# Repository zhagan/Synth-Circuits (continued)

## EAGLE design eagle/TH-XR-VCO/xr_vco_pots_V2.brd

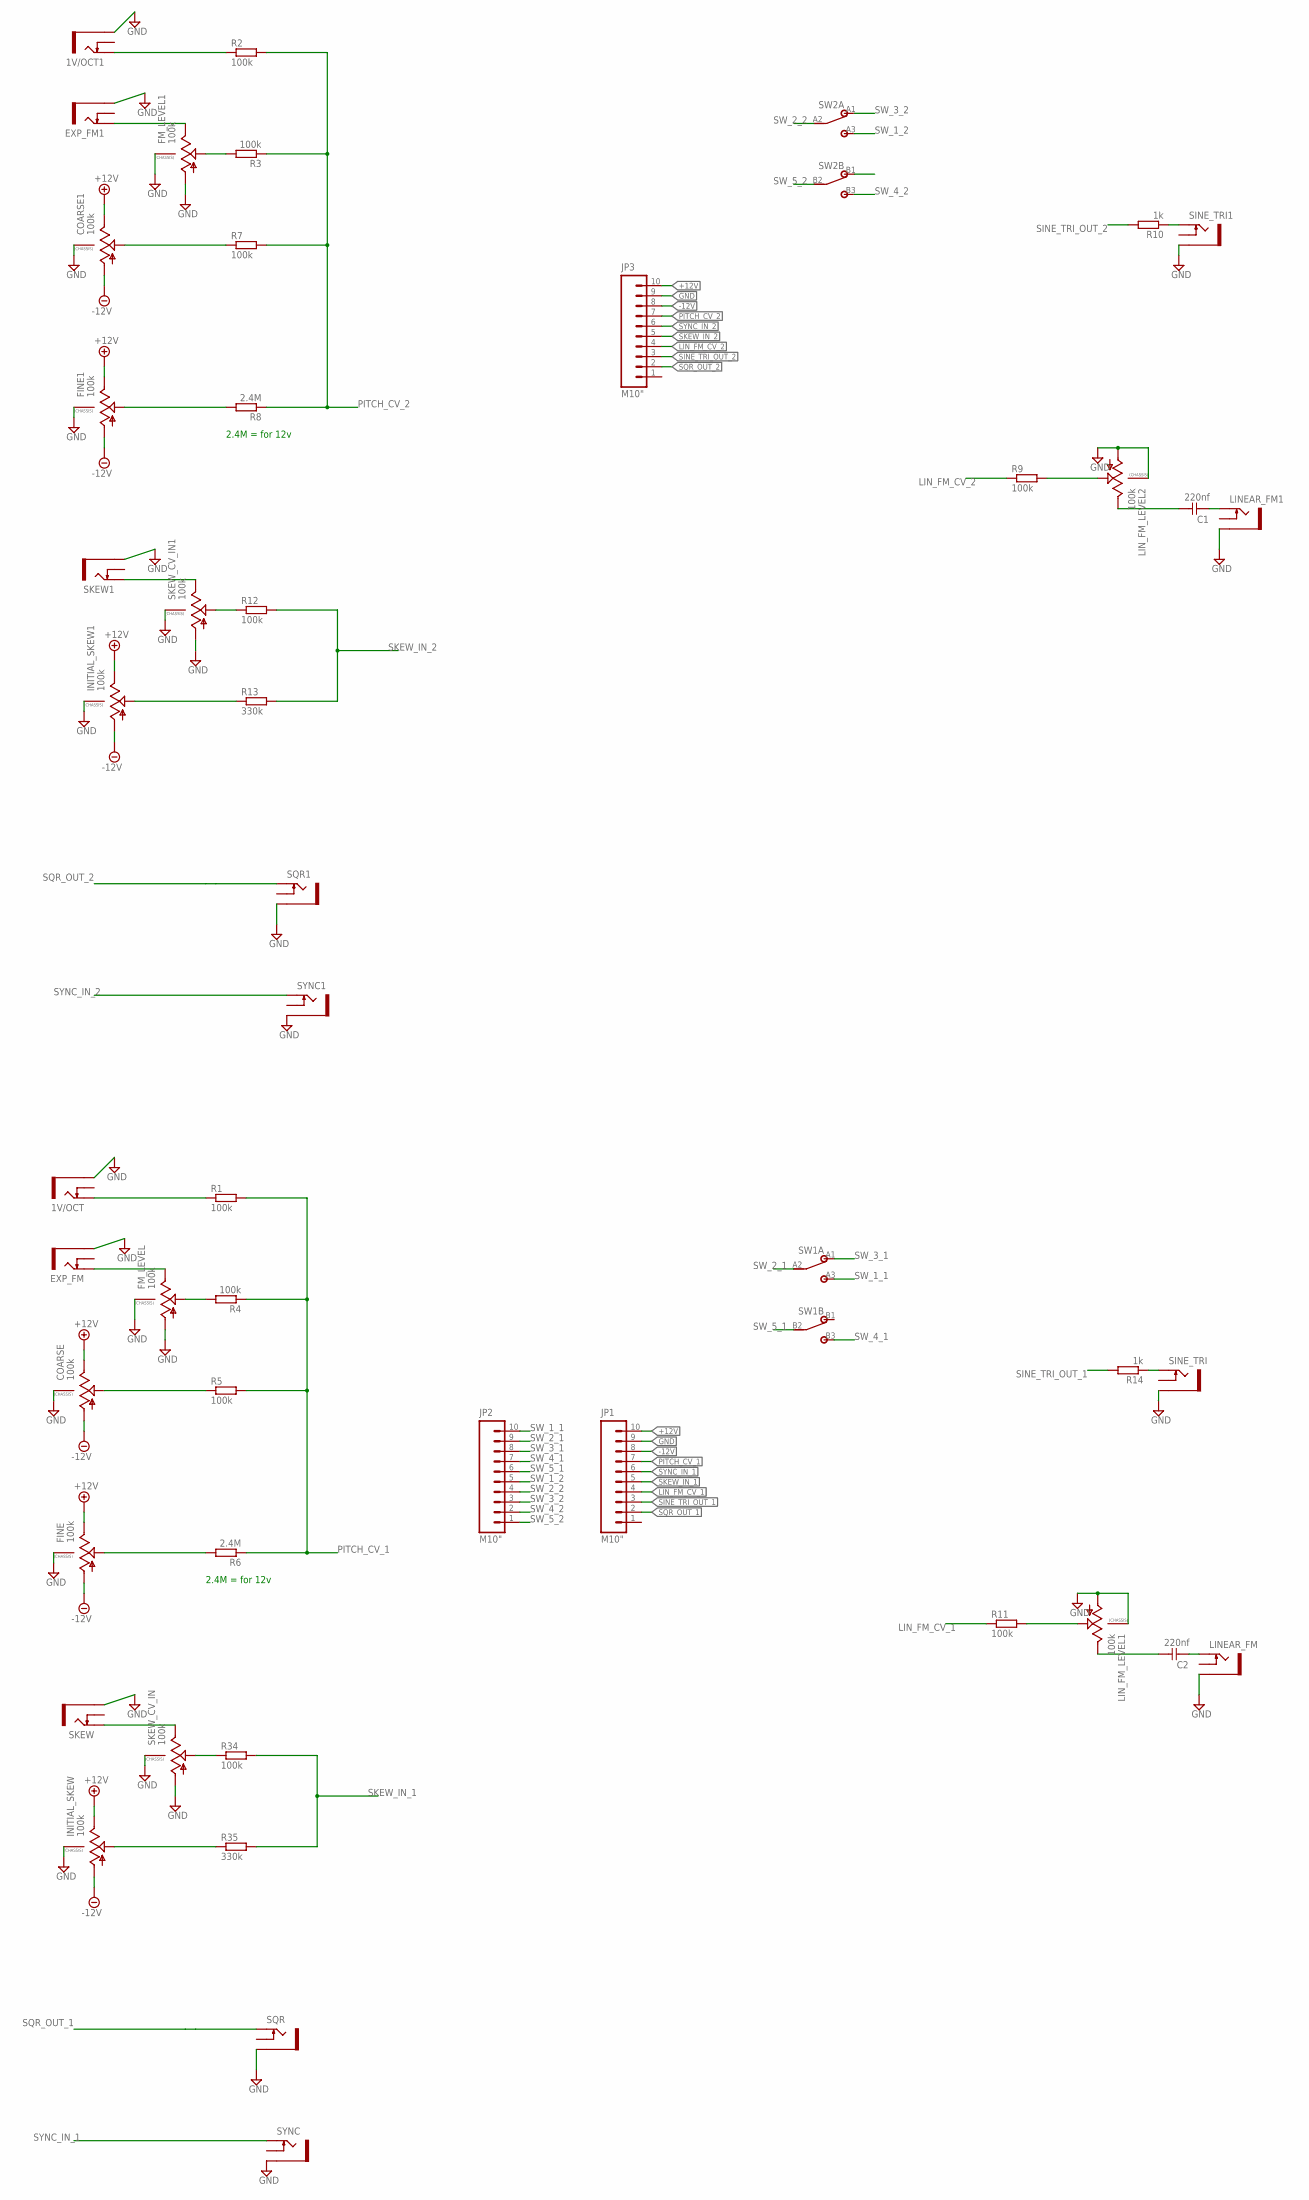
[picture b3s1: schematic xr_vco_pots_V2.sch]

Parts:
1V/OCT, 1V/OCT1: THONKICONNNEW; WQP-PJ301M-12_JACK
C1, C2: 220nf; C050-024X044
COARSE, COARSE1: 100k; 9MM_SNAP-IN_POT
EXP_FM, EXP_FM1: THONKICONNNEW; WQP-PJ301M-12_JACK
FINE, FINE1: 100k; 9MM_SNAP-IN_POT
FM_LEVEL, FM_LEVEL1: 100k; 9MM_SNAP-IN_POT
INITIAL_SKEW, INITIAL_SKEW1: 100k; 9MM_SNAP-IN_POT
JP1, JP2, JP3: M10"; 1X10
LINEAR_FM, LINEAR_FM1: THONKICONNNEW; WQP-PJ301M-12_JACK
LIN_FM_LEVEL1, LIN_FM_LEVEL2: 100k; 9MM_SNAP-IN_POT
R1, R2, R3, R4, R5, R7, R9, R11, R12, R34: 100k; 7MM_RESISTOR
R6, R8: 2.4M; 7MM_RESISTOR
R10, R14: 1k; 7MM_RESISTOR
R13, R35: 330k; 7MM_RESISTOR
SINE_TRI, SINE_TRI1: THONKICONNNEW; WQP-PJ301M-12_JACK
SKEW, SKEW1: THONKICONNNEW; WQP-PJ301M-12_JACK
SKEW_CV_IN, SKEW_CV_IN1: 100k; 9MM_SNAP-IN_POT
SQR, SQR1: THONKICONNNEW; WQP-PJ301M-12_JACK
SW1, SW2: DPDT
SYNC, SYNC1: THONKICONNNEW; WQP-PJ301M-12_JACK

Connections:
+12V: COARSE.3 (E), COARSE1.3 (E), FINE.3 (E), FINE1.3 (E), INITIAL_SKEW.3 (E), INITIAL_SKEW1.3 (E), JP1.10, JP3.10
-12V: COARSE.1 (A), COARSE1.1 (A), FINE.1 (A), FINE1.1 (A), INITIAL_SKEW.1 (A), INITIAL_SKEW1.1 (A), JP1.8, JP3.8
GND: 1V/OCT.P$3_SLEEVE (SLEEVE), 1V/OCT1.P$3_SLEEVE (SLEEVE), COARSE.CHASSIS2, COARSE1.CHASSIS2, EXP_FM.P$3_SLEEVE (SLEEVE), EXP_FM1.P$3_SLEEVE (SLEEVE), FINE.CHASSIS2, FINE1.CHASSIS2, FM_LEVEL.1 (A), FM_LEVEL.CHASSIS2, FM_LEVEL1.1 (A), FM_LEVEL1.CHASSIS2, INITIAL_SKEW.CHASSIS2, INITIAL_SKEW1.CHASSIS2, JP1.9, JP3.9, LINEAR_FM.P$3_SLEEVE (SLEEVE), LINEAR_FM1.P$3_SLEEVE (SLEEVE), LIN_FM_LEVEL1.1 (A), LIN_FM_LEVEL1.CHASSIS2, LIN_FM_LEVEL2.1 (A), LIN_FM_LEVEL2.CHASSIS2, SINE_TRI.P$3_SLEEVE (SLEEVE), SINE_TRI1.P$3_SLEEVE (SLEEVE), SKEW.P$3_SLEEVE (SLEEVE), SKEW1.P$3_SLEEVE (SLEEVE), SKEW_CV_IN.1 (A), SKEW_CV_IN.CHASSIS2, SKEW_CV_IN1.1 (A), SKEW_CV_IN1.CHASSIS2, SQR.P$3_SLEEVE (SLEEVE), SQR1.P$3_SLEEVE (SLEEVE), SYNC.P$3_SLEEVE (SLEEVE), SYNC1.P$3_SLEEVE (SLEEVE)
LIN_FM_CV_1: JP1.4, R11.1
LIN_FM_CV_2: JP3.4, R9.1
unnamed: 1V/OCT.P$1_TIP (TIP), R1.1
unnamed: EXP_FM.P$1_TIP (TIP), FM_LEVEL.3 (E)
unnamed: FM_LEVEL.2 (S), R4.2
unnamed: COARSE.2 (S), R5.1
unnamed: FINE.2 (S), R6.2
unnamed: 1V/OCT1.P$1_TIP (TIP), R2.1
unnamed: EXP_FM1.P$1_TIP (TIP), FM_LEVEL1.3 (E)
unnamed: FM_LEVEL1.2 (S), R3.2
unnamed: COARSE1.2 (S), R7.1
unnamed: FINE1.2 (S), R8.2
unnamed: LIN_FM_LEVEL2.2 (S), R9.2
unnamed: C1.1, LIN_FM_LEVEL2.3 (E)
unnamed: C1.2, LINEAR_FM1.P$1_TIP (TIP)
unnamed: R10.1, SINE_TRI1.P$1_TIP (TIP)
unnamed: SKEW1.P$1_TIP (TIP), SKEW_CV_IN1.3 (E)
unnamed: R12.1, SKEW_CV_IN1.2 (S)
unnamed: LIN_FM_LEVEL1.2 (S), R11.2
unnamed: R14.1, SINE_TRI.P$1_TIP (TIP)
unnamed: C2.1, LIN_FM_LEVEL1.3 (E)
unnamed: C2.2, LINEAR_FM.P$1_TIP (TIP)
unnamed: INITIAL_SKEW1.2 (S), R13.1
unnamed: SKEW.P$1_TIP (TIP), SKEW_CV_IN.3 (E)
unnamed: R34.1, SKEW_CV_IN.2 (S)
unnamed: INITIAL_SKEW.2 (S), R35.1
PITCH_CV_1: JP1.7, R1.2, R4.1, R5.2, R6.1
PITCH_CV_2: JP3.7, R2.2, R3.1, R7.2, R8.1
SINE_TRI_OUT_1: JP1.3, R14.2
SINE_TRI_OUT_2: JP3.3, R10.2
SKEW_IN_1: JP1.5, R34.2, R35.2
SKEW_IN_2: JP3.5, R12.2, R13.2
SQR_OUT_1: JP1.2, SQR.P$1_TIP (TIP)
SQR_OUT_2: JP3.2, SQR1.P$1_TIP (TIP)
SW_1_1: JP2.10, SW1.A3 (3)
SW_1_2: JP2.5, SW2.A3 (3)
SW_2_1: JP2.9, SW1.A2 (2)
SW_2_2: JP2.4, SW2.A2 (2)
SW_3_1: JP2.8, SW1.A1 (1)
SW_3_2: JP2.3, SW2.A1 (1)
SW_4_1: JP2.7, SW1.B3 (3)
SW_4_2: JP2.2, SW2.B3 (3)
SW_5_1: JP2.6, SW1.B2 (2)
SW_5_2: JP2.1, SW2.B2 (2)
SW_6: SW2.B1 (1)
SYNC_IN_1: JP1.6, SYNC.P$1_TIP (TIP)
SYNC_IN_2: JP3.6, SYNC1.P$1_TIP (TIP)

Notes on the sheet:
2.4M = for 12v

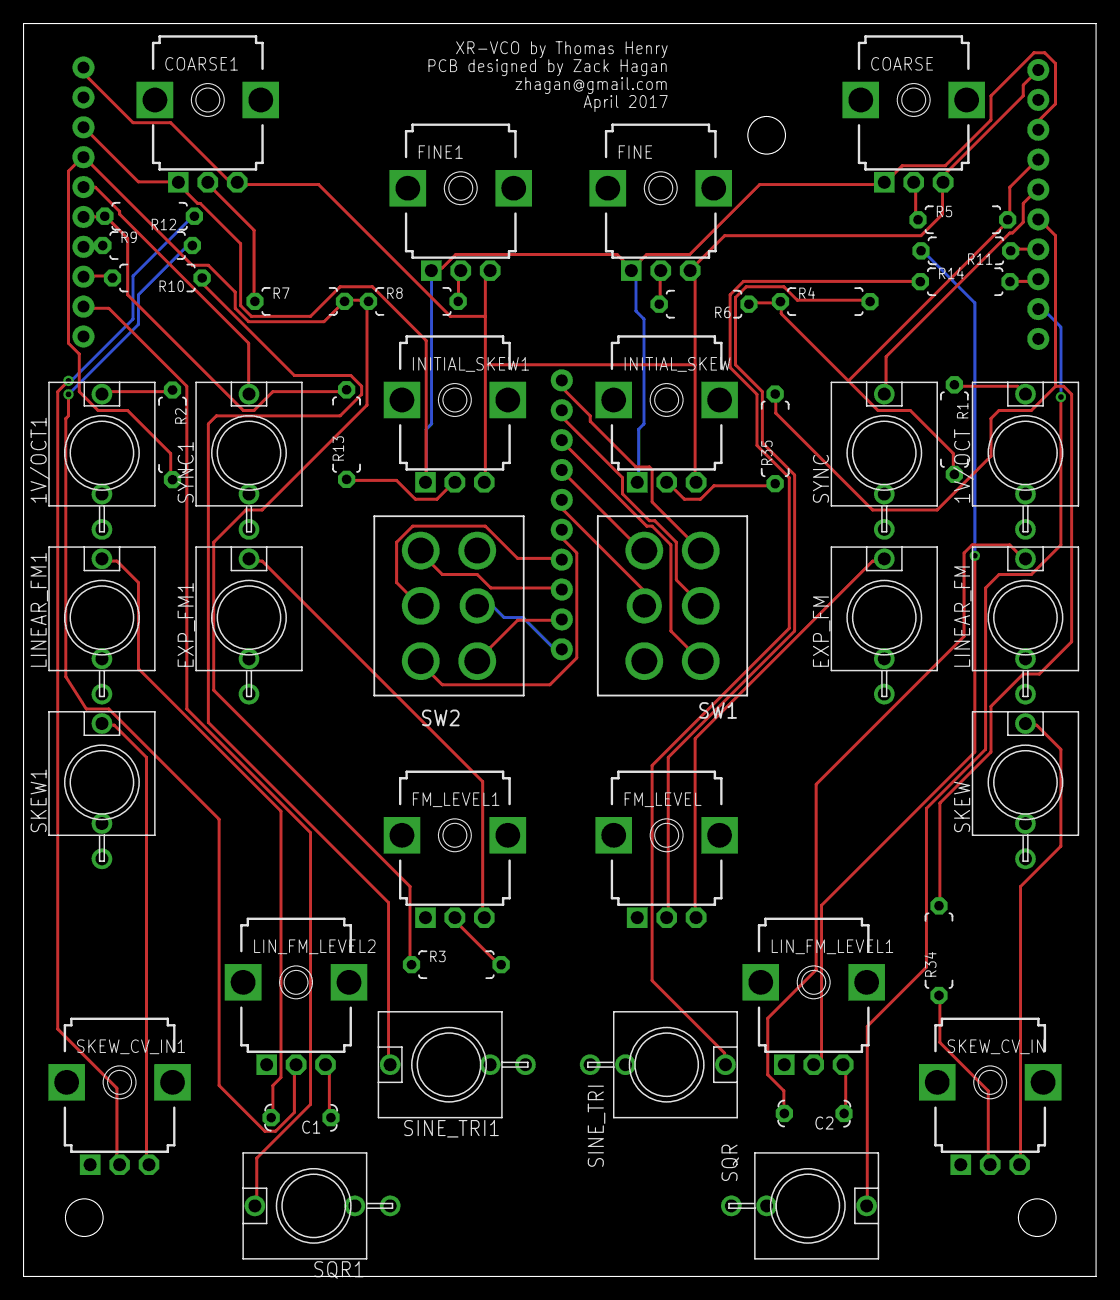
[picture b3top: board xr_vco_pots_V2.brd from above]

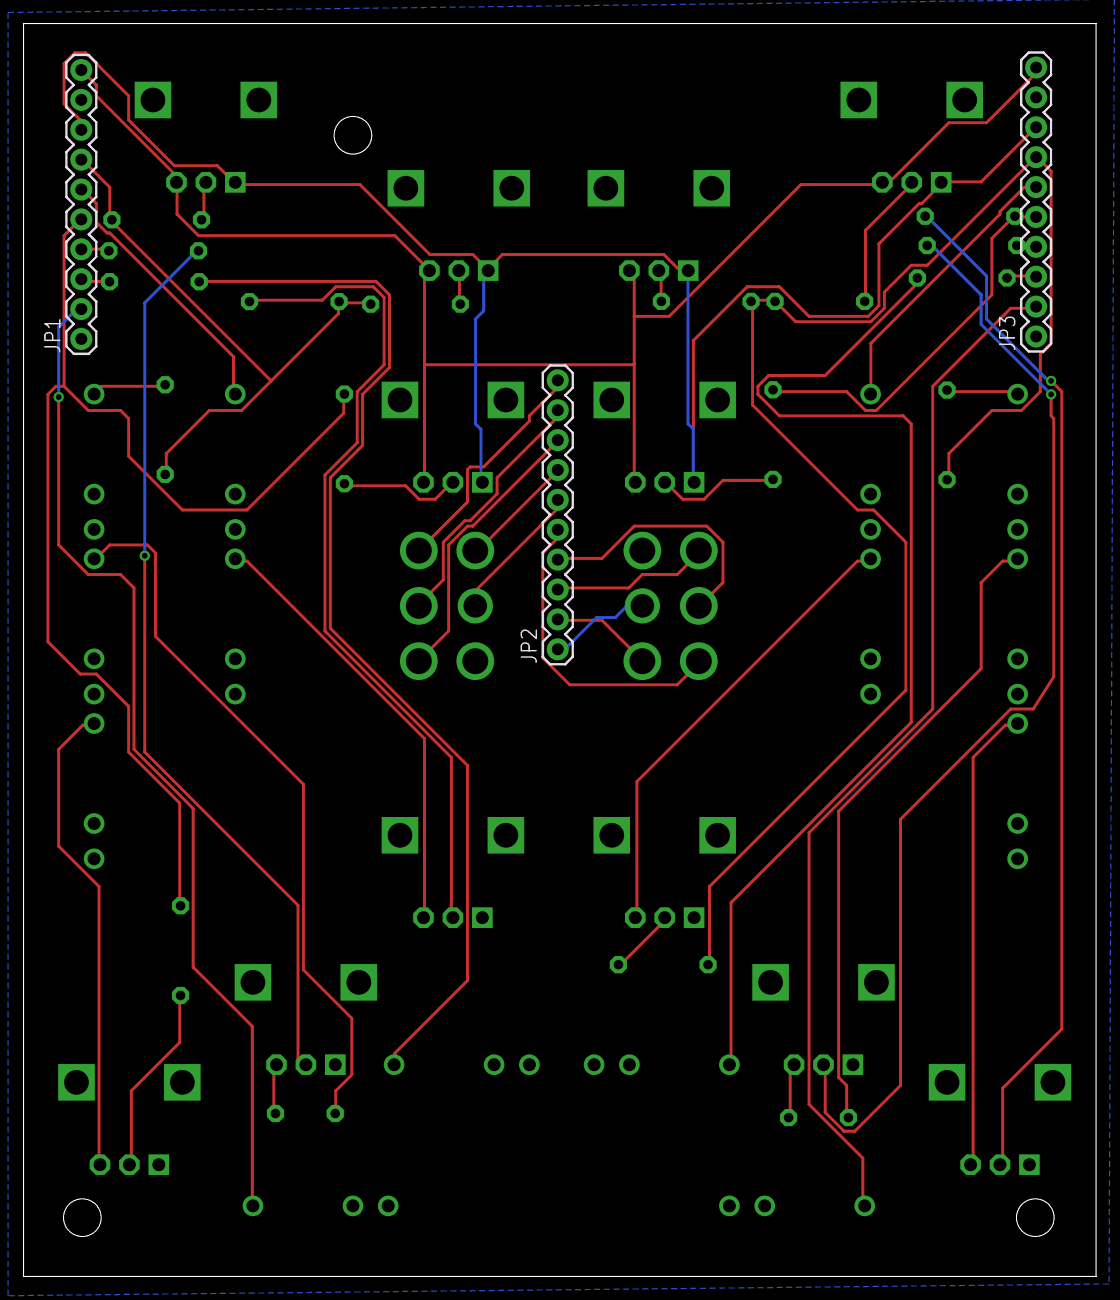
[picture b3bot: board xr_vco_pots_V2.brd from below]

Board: 2 copper layers, 91.2 x 106.5 mm, 52 parts (3 on the bottom side), 49 nets.

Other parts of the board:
U$1, U$3, U$4: MOUNTING_HOLE

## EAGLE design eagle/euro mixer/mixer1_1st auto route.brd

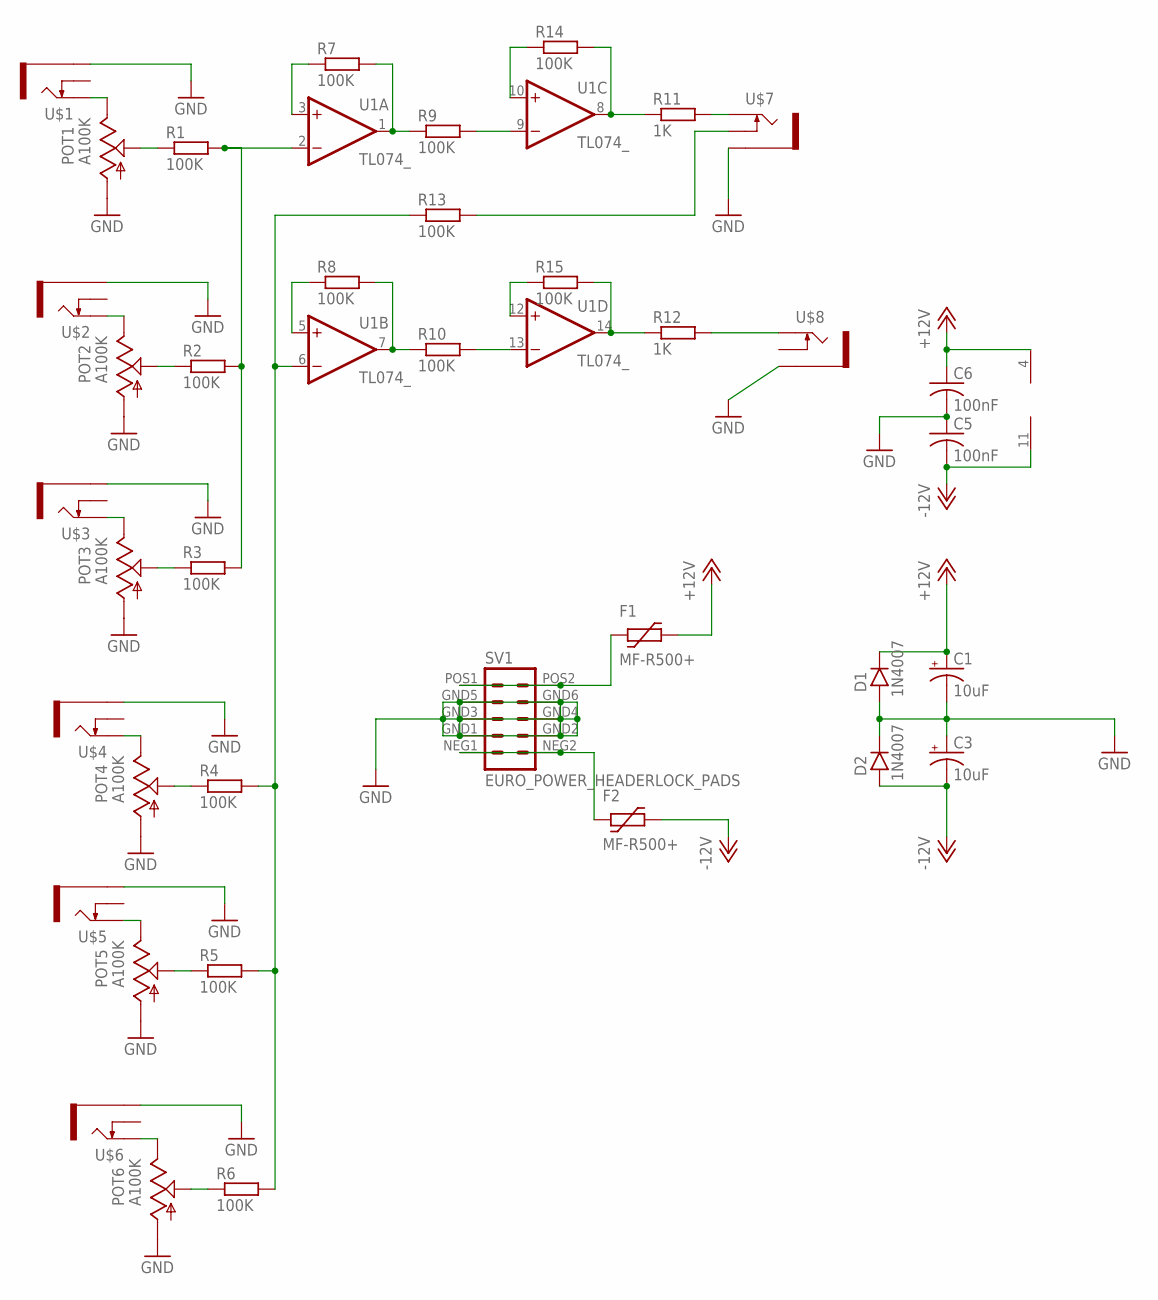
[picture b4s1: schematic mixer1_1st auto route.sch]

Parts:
C1, C3: 10uF; E2,5-7
C5, C6: 100nF; C075-032X103
D1, D2: 1N4007; DO41-3
F1, F2: MF-R500+; BOURNS-MF-R
POT1, POT2, POT3, POT4, POT5, POT6: A100K; 9MM_SNAP-IN_POT
R1, R2, R3, R4, R5, R6, R7, R8, R9, R10, R13, R14, R15: 100K; 7MM_RESISTOR
R11, R12: 1K; 7MM_RESISTOR
SV1: EURO_POWER_HEADERLOCK_PADS; EURO_PWR_HEADER_LOCK
U1: TL074_; DIL14
U$1, U$2, U$3, U$4, U$5, U$6, U$7, U$8: THONKICONNNEW; WQP-PJ301M-12_JACK

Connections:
+12V: C1.+, C6.1, D1.C, F1.P$2 (2), U1.4 (V+)
-12V: C3.-, C5.2, D2.A, F2.P$2 (2), U1.11 (V-)
GND: C1.-, C3.+, C5.1, C6.2, D1.A, D2.C, POT1.1 (A), POT2.1 (A), POT3.1 (A), POT4.1 (A), POT5.1 (A), POT6.1 (A), SV1.GND1 (4), SV1.GND2 (3), SV1.GND3 (6), SV1.GND4 (5), SV1.GND5 (8), SV1.GND6 (7), U$1.P$3_SLEEVE (SLEEVE), U$2.P$3_SLEEVE (SLEEVE), U$3.P$3_SLEEVE (SLEEVE), U$4.P$3_SLEEVE (SLEEVE), U$5.P$3_SLEEVE (SLEEVE), U$6.P$3_SLEEVE (SLEEVE), U$7.P$3_SLEEVE (SLEEVE), U$8.P$3_SLEEVE (SLEEVE)
unnamed: POT2.3 (E), U$2.P$1_TIP (TIP)
unnamed: POT2.2 (S), R2.1
unnamed: POT1.3 (E), U$1.P$1_TIP (TIP)
unnamed: POT1.2 (S), R1.1
unnamed: POT3.3 (E), U$3.P$1_TIP (TIP)
unnamed: POT3.2 (S), R3.1
unnamed: POT4.3 (E), U$4.P$1_TIP (TIP)
unnamed: POT4.2 (S), R4.1
unnamed: POT5.3 (E), U$5.P$1_TIP (TIP)
unnamed: POT5.2 (S), R5.1
unnamed: POT6.3 (E), U$6.P$1_TIP (TIP)
unnamed: POT6.2 (S), R6.1
unnamed: R1.2, R2.2, R3.2, U1.2 (-IN)
unnamed: R7.1, U1.3 (+IN)
unnamed: R7.2, R9.1, U1.1 (OUT)
unnamed: R9.2, U1.9 (-IN)
unnamed: R14.1, U1.10 (+IN)
unnamed: R11.2, U$7.P$1_TIP (TIP)
unnamed: R8.2, R10.1, U1.7 (OUT)
unnamed: R8.1, U1.5 (+IN)
unnamed: R15.1, U1.12 (+IN)
unnamed: R12.1, R15.2, U1.14 (OUT)
unnamed: R10.2, U1.13 (-IN)
unnamed: R4.2, R5.2, R6.2, R13.1, U1.6 (-IN)
unnamed: R11.1, R14.2, U1.8 (OUT)
unnamed: R13.2, U$7.P$2_SWITCH (SWITCH)
unnamed: R12.2, U$8.P$1_TIP (TIP)
unnamed: F2.P$1 (1), SV1.NEG1 (2), SV1.NEG2 (1)
unnamed: F1.P$1 (1), SV1.POS1 (10), SV1.POS2 (9)

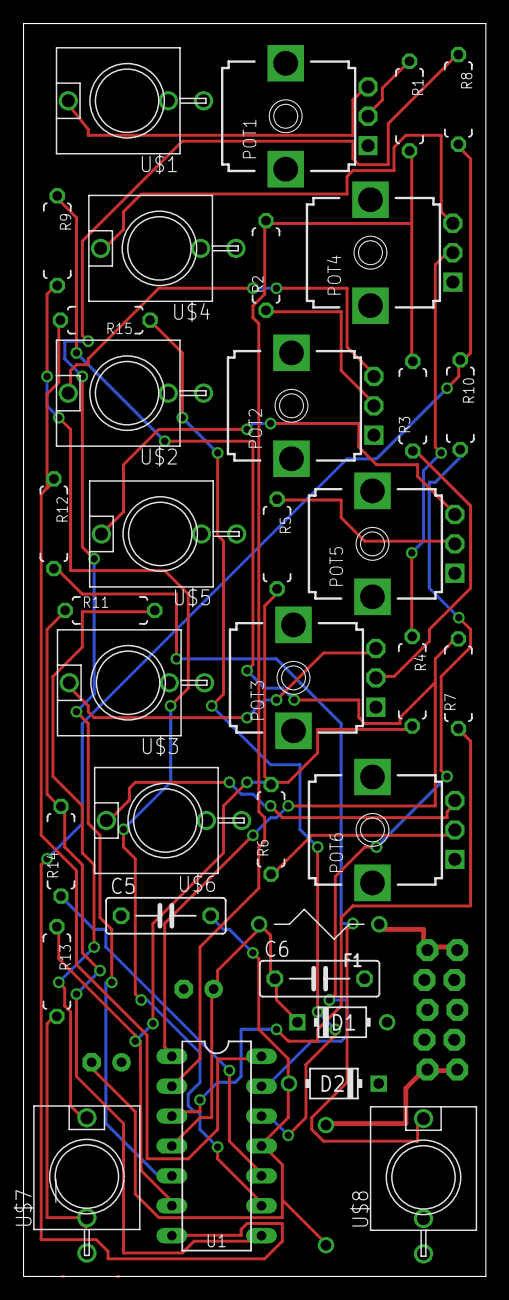
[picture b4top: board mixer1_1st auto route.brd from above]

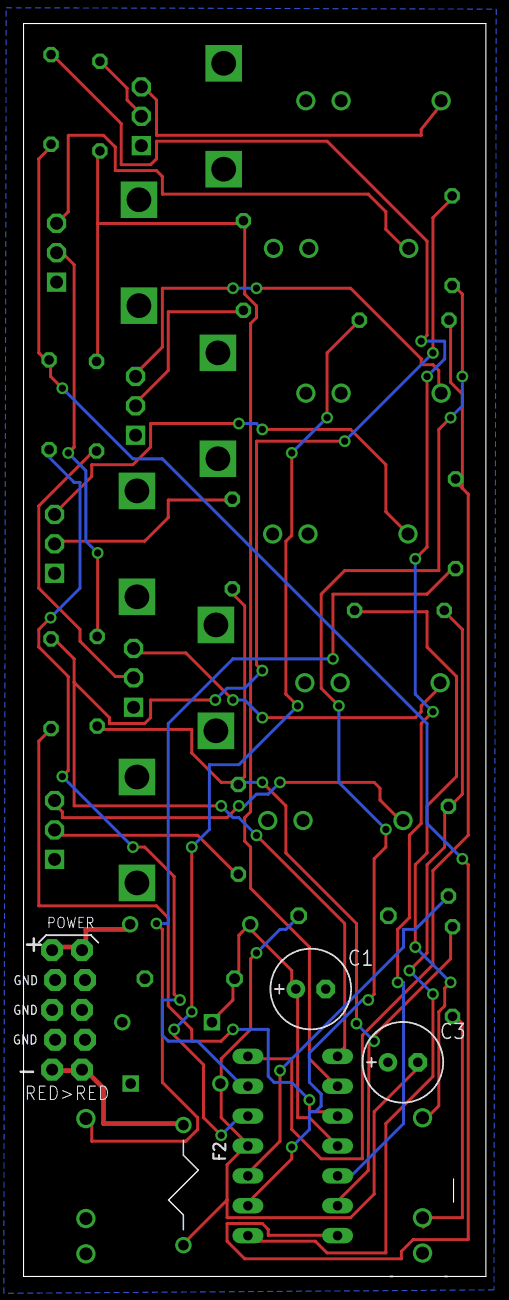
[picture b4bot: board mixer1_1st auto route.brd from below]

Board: 2 copper layers, 39.3 x 106.5 mm, 39 parts (4 on the bottom side), 32 nets.

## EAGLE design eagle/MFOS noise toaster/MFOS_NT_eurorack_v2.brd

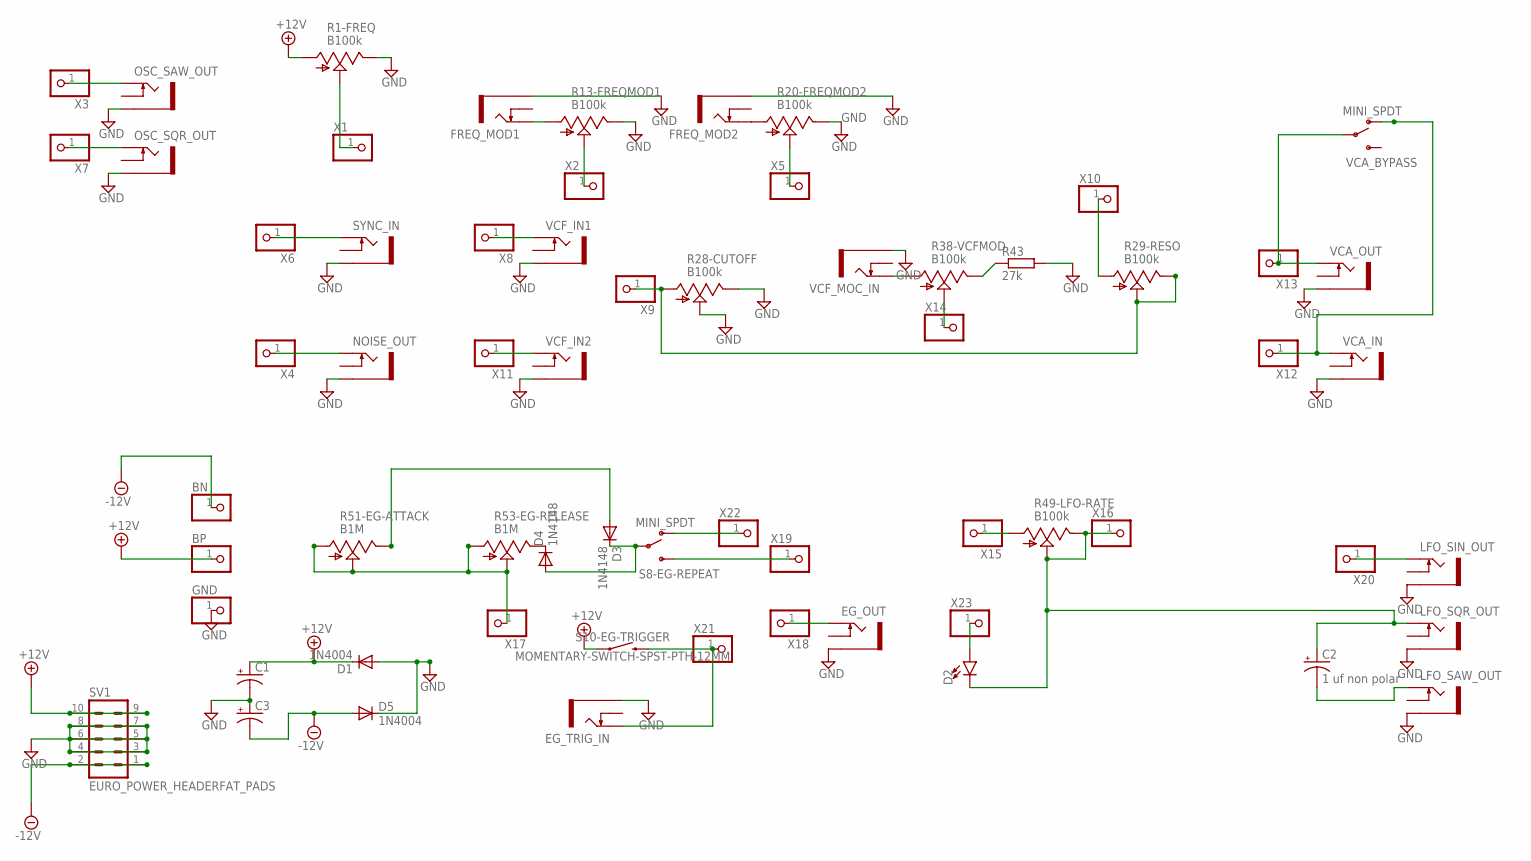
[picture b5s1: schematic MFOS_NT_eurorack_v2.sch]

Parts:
BN: PINHD-1X1; 1X01
BP: PINHD-1X1; 1X01
C1, C3: CPOL-USE2.5-7; E2,5-7
C2: 1 uf non polar; TT2D5L
D1, D5: 1N4004; DO41-10
D2: LED3MM; LED_3MM
D3, D4: 1N4148; DO35-7
EG_OUT: THONKICONNNEW; WQP-PJ301M-12_JACK
EG_TRIG_IN: THONKICONNNEW; WQP-PJ301M-12_JACK
FREQ_MOD1, FREQ_MOD2: THONKICONNNEW; WQP-PJ301M-12_JACK
GND: PINHD-1X1; 1X01
LFO_SAW_OUT: THONKICONNNEW; WQP-PJ301M-12_JACK
LFO_SIN_OUT: THONKICONNNEW; WQP-PJ301M-12_JACK
LFO_SQR_OUT: THONKICONNNEW; WQP-PJ301M-12_JACK
NOISE_OUT: THONKICONNNEW; WQP-PJ301M-12_JACK
OSC_SAW_OUT: THONKICONNNEW; WQP-PJ301M-12_JACK
OSC_SQR_OUT: THONKICONNNEW; WQP-PJ301M-12_JACK
R1-FREQ, R13-FREQMOD1, R20-FREQMOD2, R28-CUTOFF, R29-RESO, R38-VCFMOD, R49-LFO-RATE: B100k; 9MM_SNAP-IN_POT
R43: 27k; 7MM_RESISTOR
R51-EG-ATTACK, R53-EG-RELEASE: B1M; 9MM_SNAP-IN_POT
S8-EG-REPEAT: MINI_SPDT; MINI_SPDT_RIGHTANGLE
S10-EG-TRIGGER: MOMENTARY-SWITCH-SPST-PTH-12MM; TACTILE_SWITCH_PTH_12MM
SV1: EURO_POWER_HEADERFAT_PADS; EURO_PWR_HEADER_FAT
SYNC_IN: THONKICONNNEW; WQP-PJ301M-12_JACK
VCA_BYPASS: MINI_SPDT; MINI_SPDT_RIGHTANGLE
VCA_IN: THONKICONNNEW; WQP-PJ301M-12_JACK
VCA_OUT: THONKICONNNEW; WQP-PJ301M-12_JACK
VCF_IN1, VCF_IN2: THONKICONNNEW; WQP-PJ301M-12_JACK
VCF_MOC_IN: THONKICONNNEW; WQP-PJ301M-12_JACK
X1, X2, X3, X4, X5, X6, X7, X8, X9, X10, X11, X12, X13, X14, X15, X16, X17, X18, X19, X20, X21, X22, X23: PINHD-1X1; 1X01

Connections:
+12V: BP.1, C1.+, D1.C, R1-FREQ.1 (A), S10-EG-TRIGGER.1, SV1.9, SV1.10
-12V: BN.1, C3.-, D5.A, SV1.1, SV1.2
GND: C1.-, C3.+, D1.A, D5.C, EG_OUT.P$3_SLEEVE (SLEEVE), EG_TRIG_IN.P$3_SLEEVE (SLEEVE), FREQ_MOD1.P$3_SLEEVE (SLEEVE), FREQ_MOD2.P$3_SLEEVE (SLEEVE), GND.1, LFO_SAW_OUT.P$3_SLEEVE (SLEEVE), LFO_SIN_OUT.P$3_SLEEVE (SLEEVE), LFO_SQR_OUT.P$3_SLEEVE (SLEEVE), NOISE_OUT.P$3_SLEEVE (SLEEVE), OSC_SAW_OUT.P$3_SLEEVE (SLEEVE), OSC_SQR_OUT.P$3_SLEEVE (SLEEVE), R1-FREQ.3 (E), R13-FREQMOD1.3 (E), R20-FREQMOD2.3 (E), R28-CUTOFF.2 (S), R28-CUTOFF.3 (E), R43.2, SV1.3, SV1.4, SV1.5, SV1.6, SV1.7, SV1.8, SYNC_IN.P$3_SLEEVE (SLEEVE), VCA_IN.P$3_SLEEVE (SLEEVE), VCA_OUT.P$3_SLEEVE (SLEEVE), VCF_IN1.P$3_SLEEVE (SLEEVE), VCF_IN2.P$3_SLEEVE (SLEEVE), VCF_MOC_IN.P$3_SLEEVE (SLEEVE)
unnamed: R1-FREQ.2 (S), X1.1
unnamed: FREQ_MOD1.P$1_TIP (TIP), R13-FREQMOD1.1 (A)
unnamed: FREQ_MOD2.P$1_TIP (TIP), R20-FREQMOD2.1 (A)
unnamed: R13-FREQMOD1.2 (S), X2.1
unnamed: R20-FREQMOD2.2 (S), X5.1
unnamed: SYNC_IN.P$1_TIP (TIP), X6.1
unnamed: OSC_SAW_OUT.P$1_TIP (TIP), X3.1
unnamed: OSC_SQR_OUT.P$1_TIP (TIP), X7.1
unnamed: NOISE_OUT.P$1_TIP (TIP), X4.1
unnamed: VCF_IN1.P$1_TIP (TIP), X8.1
unnamed: VCF_IN2.P$1_TIP (TIP), X11.1
unnamed: R28-CUTOFF.1 (A), R29-RESO.2 (S), R29-RESO.3 (E), X9.1
unnamed: R38-VCFMOD.3 (E), R43.1
unnamed: R29-RESO.1 (A), X10.1
unnamed: R38-VCFMOD.2 (S), X14.1
unnamed: R38-VCFMOD.1 (A), VCF_MOC_IN.P$1_TIP (TIP)
unnamed: VCA_BYPASS.UP (O), VCA_IN.P$1_TIP (TIP), X12.1
unnamed: VCA_BYPASS.COMMON, VCA_OUT.P$1_TIP (TIP), X13.1
unnamed: EG_TRIG_IN.P$1_TIP (TIP), S10-EG-TRIGGER.3 (2), X21.1
unnamed: R51-EG-ATTACK.1 (A), R51-EG-ATTACK.2 (S), R53-EG-RELEASE.1 (A), R53-EG-RELEASE.2 (S), X17.1
unnamed: D4.C, R53-EG-RELEASE.3 (E)
unnamed: D3.C, D4.A, S8-EG-REPEAT.COMMON
unnamed: S8-EG-REPEAT.DOWN (S), X19.1
unnamed: D3.A, R51-EG-ATTACK.3 (E)
unnamed: S8-EG-REPEAT.UP (O), X22.1
unnamed: EG_OUT.P$1_TIP (TIP), X18.1
unnamed: R49-LFO-RATE.1 (A), X15.1
unnamed: C2.+, D2.K (C), LFO_SQR_OUT.P$1_TIP (TIP), R49-LFO-RATE.2 (S), R49-LFO-RATE.3 (E), X16.1
unnamed: C2.-, LFO_SAW_OUT.P$1_TIP (TIP)
unnamed: LFO_SIN_OUT.P$1_TIP (TIP), X20.1
unnamed: D2.A, X23.1

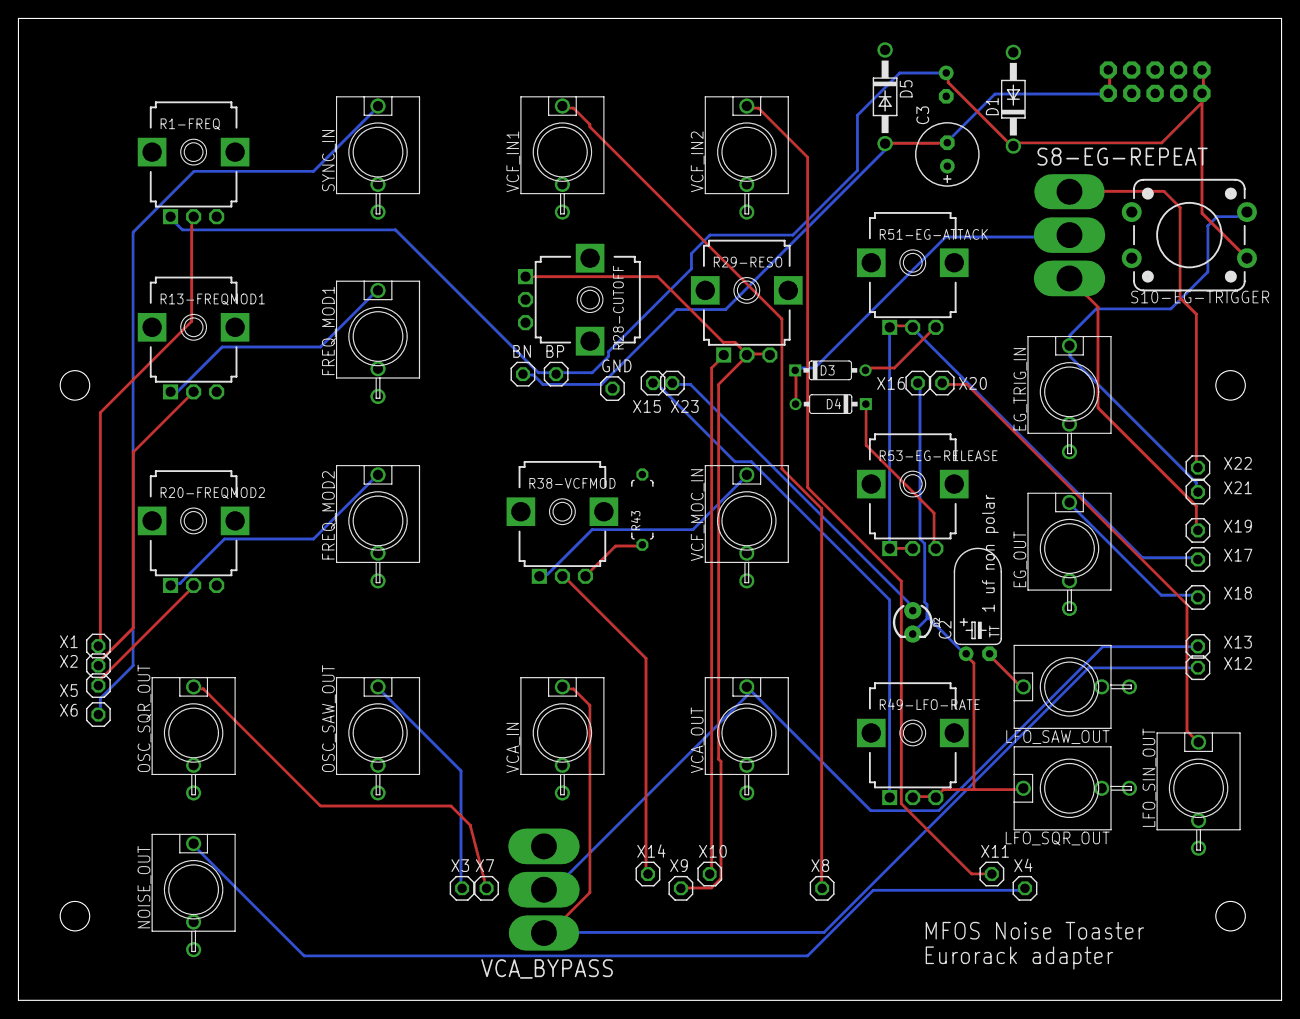
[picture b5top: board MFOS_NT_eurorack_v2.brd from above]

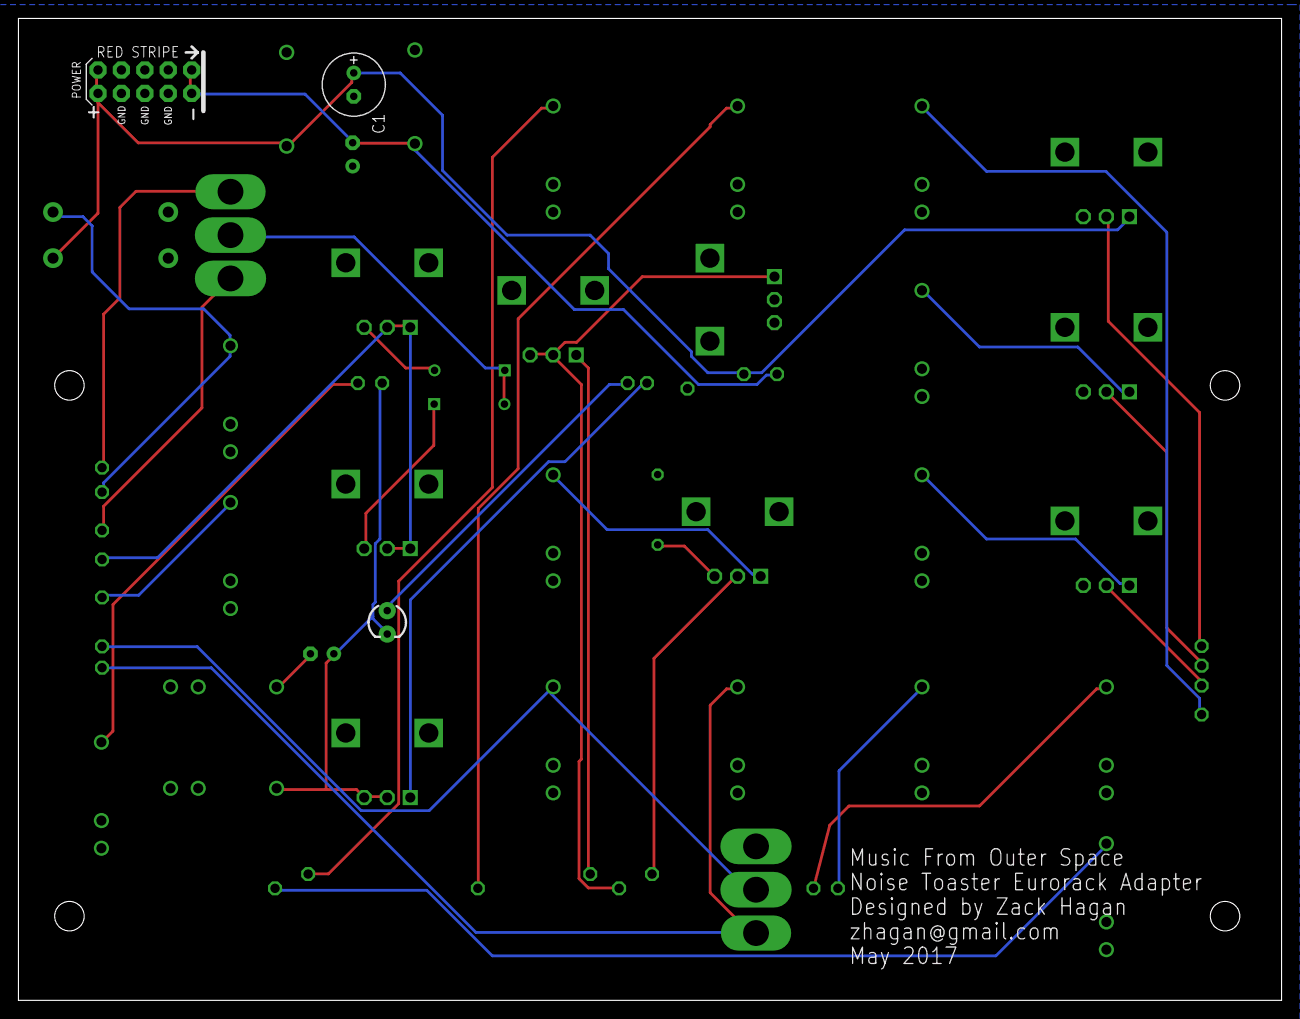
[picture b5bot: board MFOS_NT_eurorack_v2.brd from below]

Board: 2 copper layers, 137.0 x 106.5 mm, 68 parts (2 on the bottom side), 34 nets.

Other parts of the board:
U$1, U$2, U$3, U$4: MOUNTING_HOLE

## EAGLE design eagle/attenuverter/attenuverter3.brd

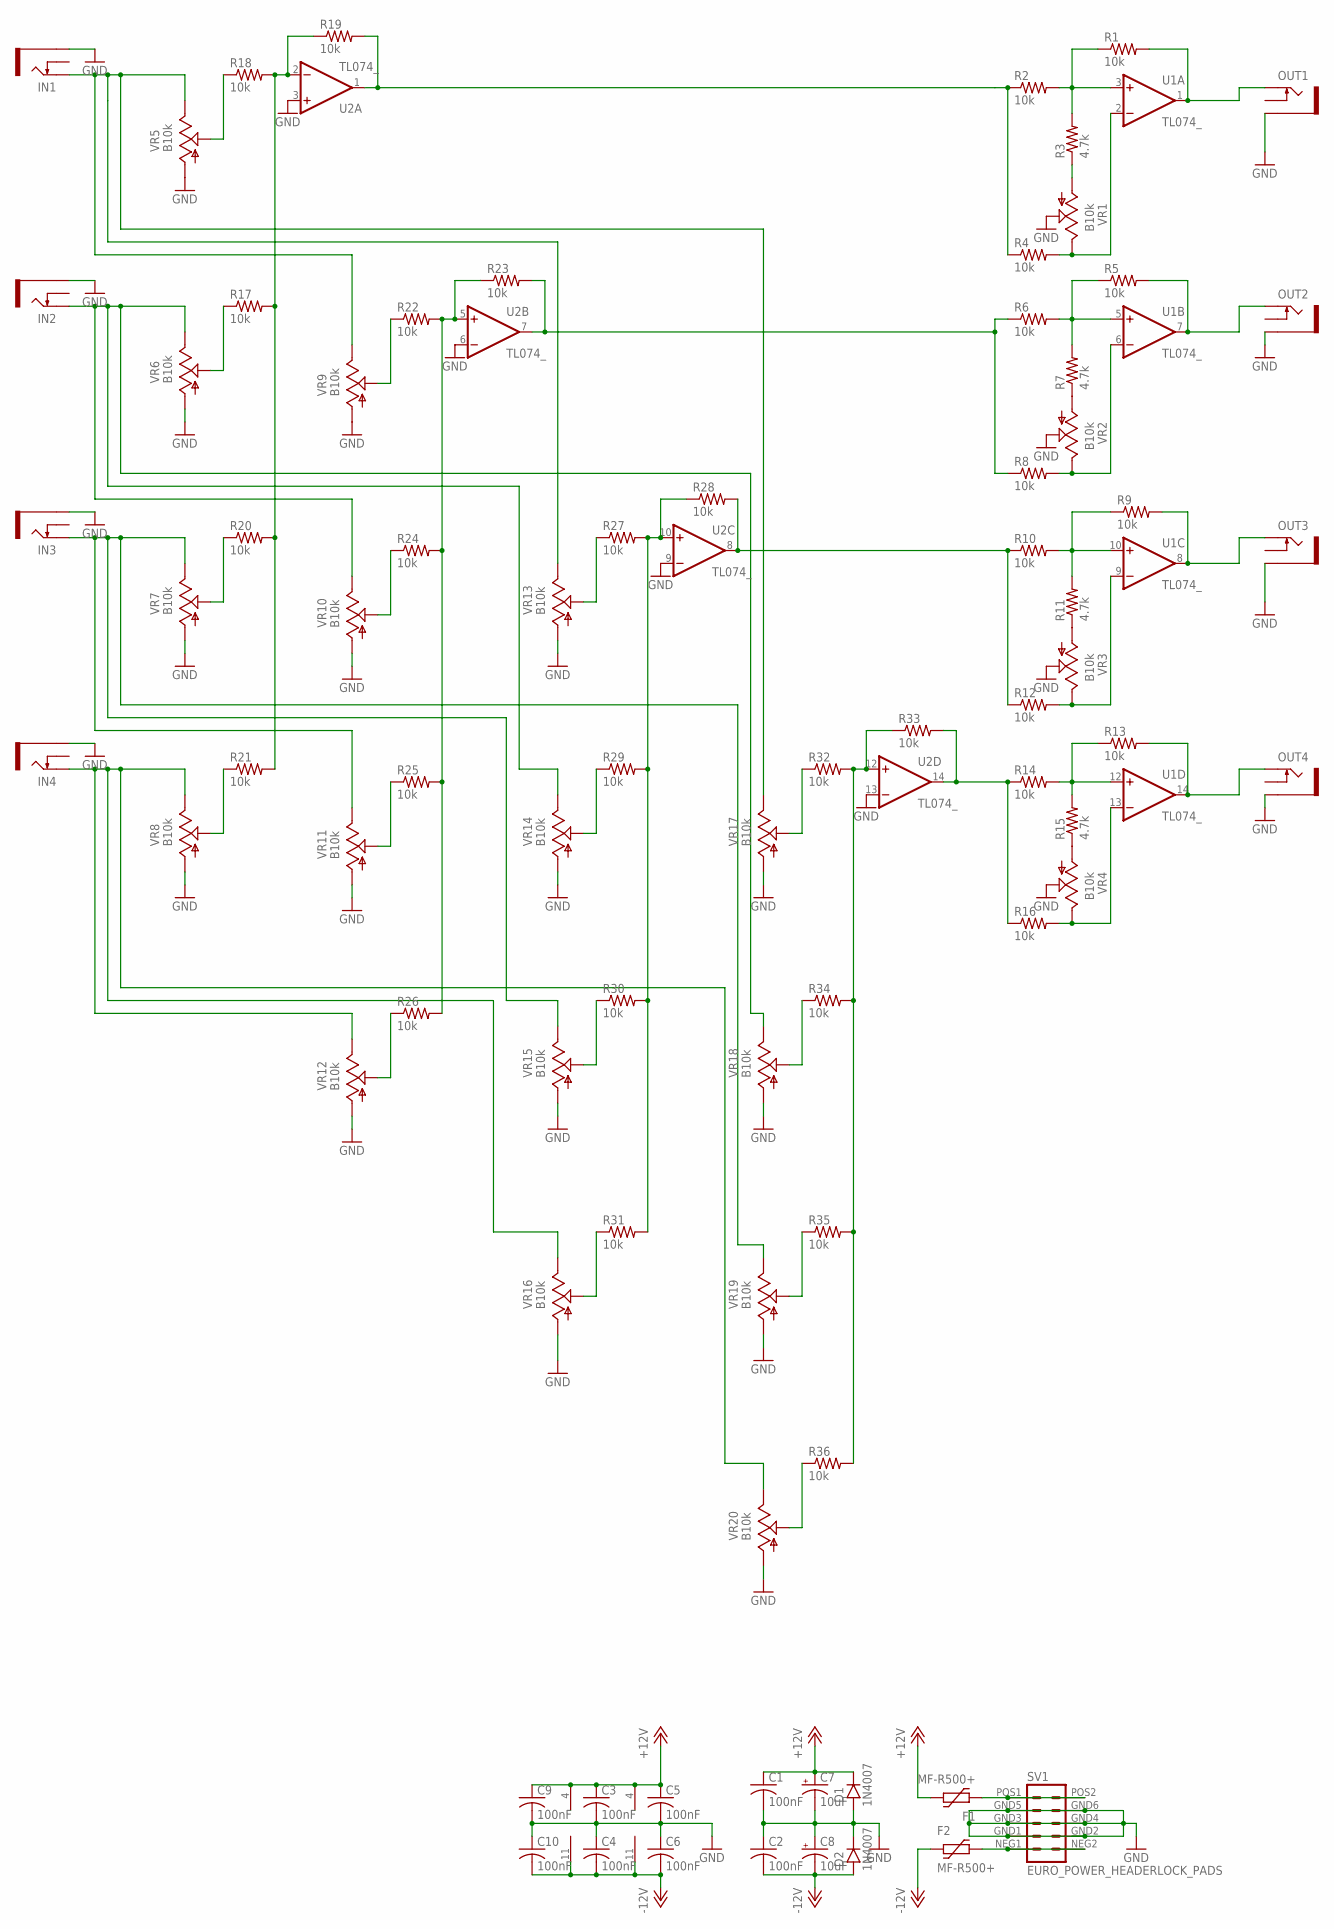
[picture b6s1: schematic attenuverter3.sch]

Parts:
C1, C2, C3, C4, C5, C6, C9, C10: 100nF; C050-055X075
C7, C8: 10uF; E2,5-6
D1, D2: 1N4007; DO41-4
F1, F2: MF-R500+; BOURNS-MF-R
IN1, IN2, IN3, IN4: THONKICONNNEW; WQP-PJ301M-12_JACK
OUT1, OUT2, OUT3, OUT4: THONKICONNNEW; WQP-PJ301M-12_JACK
R1, R2, R4, R5, R6, R8, R9, R10, R12, R13, R14, R16, R17, R18, R19, R20, R21, R22, R23, R24, R25, R26, R27, R28, R29, R30, R31, R32, R33, R34, R35, R36: 10k; 0207/7
R3, R7, R11, R15: 4.7k; 0207/7
SV1: EURO_POWER_HEADERLOCK_PADS; EURO_PWR_HEADER_LOCK
U1, U2: TL074_; DIL14
VR1, VR2, VR3, VR4, VR5, VR6, VR7, VR8, VR9, VR10, VR11, VR12, VR13, VR14, VR15, VR16, VR17, VR18, VR19, VR20: B10k; 9MM_SNAP-IN_POT

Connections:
+12V: C1.1, C3.1, C5.1, C7.+, C9.1, D1.C, F1.P$2 (2), U1.4 (V+), U2.4 (V+)
-12V: C2.2, C4.2, C6.2, C8.-, C10.2, D2.A, F2.P$1 (1), U1.11 (V-), U2.11 (V-)
GND: C1.2, C2.1, C3.2, C4.1, C5.2, C6.1, C7.-, C8.+, C9.2, C10.1, D1.A, D2.C, IN1.P$3_SLEEVE (SLEEVE), IN2.P$3_SLEEVE (SLEEVE), IN3.P$3_SLEEVE (SLEEVE), IN4.P$3_SLEEVE (SLEEVE), OUT1.P$3_SLEEVE (SLEEVE), OUT2.P$3_SLEEVE (SLEEVE), OUT3.P$3_SLEEVE (SLEEVE), OUT4.P$3_SLEEVE (SLEEVE), SV1.GND1 (4), SV1.GND2 (3), SV1.GND3 (6), SV1.GND4 (5), SV1.GND5 (8), SV1.GND6 (7), U2.3 (+IN), U2.6 (-IN), U2.9 (-IN), U2.13 (-IN), VR1.2 (S), VR2.2 (S), VR3.2 (S), VR4.2 (S), VR5.1 (A), VR6.1 (A), VR7.1 (A), VR8.1 (A), VR9.1 (A), VR10.1 (A), VR11.1 (A), VR12.1 (A), VR13.1 (A), VR14.1 (A), VR15.1 (A), VR16.1 (A), VR17.1 (A), VR18.1 (A), VR19.1 (A), VR20.1 (A)
unnamed: R1.1, R2.2, R3.2, U1.3 (+IN)
unnamed: R2.1, R4.1, R19.2, U2.1 (OUT)
unnamed: R4.2, U1.2 (-IN), VR1.3 (E)
unnamed: R3.1, VR1.1 (A)
unnamed: R22.2, R23.1, R24.2, R25.2, R26.2, U2.5 (+IN)
unnamed: R5.1, R6.2, R7.2, U1.5 (+IN)
unnamed: OUT1.P$1_TIP (TIP), R1.2, U1.1 (OUT)
unnamed: R8.2, U1.6 (-IN), VR2.3 (E)
unnamed: F1.P$1 (1), SV1.POS1 (10), SV1.POS2 (9)
unnamed: F2.P$2 (2), SV1.NEG1 (2), SV1.NEG2 (1)
unnamed: R7.1, VR2.1 (A)
unnamed: OUT2.P$1_TIP (TIP), R5.2, U1.7 (OUT)
unnamed: R22.1, VR9.2 (S)
unnamed: R9.1, R10.2, R11.2, U1.10 (+IN)
unnamed: R12.2, U1.9 (-IN), VR3.3 (E)
unnamed: R11.1, VR3.1 (A)
unnamed: OUT3.P$1_TIP (TIP), R9.2, U1.8 (OUT)
unnamed: IN4.P$1_TIP (TIP), VR8.3 (E), VR12.3 (E), VR16.3 (E), VR20.3 (E)
unnamed: R13.1, R14.2, R15.2, U1.12 (+IN)
unnamed: R16.2, U1.13 (-IN), VR4.3 (E)
unnamed: R15.1, VR4.1 (A)
unnamed: OUT4.P$1_TIP (TIP), R13.2, U1.14 (OUT)
unnamed: IN2.P$1_TIP (TIP), VR6.3 (E), VR10.3 (E), VR14.3 (E), VR18.3 (E)
unnamed: R17.2, R18.2, R19.1, R20.2, R21.2, U2.2 (-IN)
unnamed: R18.1, VR5.2 (S)
unnamed: R17.1, VR6.2 (S)
unnamed: IN3.P$1_TIP (TIP), VR7.3 (E), VR11.3 (E), VR15.3 (E), VR19.3 (E)
unnamed: R20.1, VR7.2 (S)
unnamed: R21.1, VR8.2 (S)
unnamed: R24.1, VR10.2 (S)
unnamed: R25.1, VR11.2 (S)
unnamed: R26.1, VR12.2 (S)
unnamed: IN1.P$1_TIP (TIP), VR5.3 (E), VR9.3 (E), VR13.3 (E), VR17.3 (E)
unnamed: R6.1, R8.1, R23.2, U2.7 (OUT)
unnamed: R27.2, R28.1, R29.2, R30.2, R31.2, U2.10 (+IN)
unnamed: R27.1, VR13.2 (S)
unnamed: R29.1, VR14.2 (S)
unnamed: R30.1, VR15.2 (S)
unnamed: R31.1, VR16.2 (S)
unnamed: R10.1, R12.1, R28.2, U2.8 (OUT)
unnamed: R32.2, R33.1, R34.2, R35.2, R36.2, U2.12 (+IN)
unnamed: R32.1, VR17.2 (S)
unnamed: R34.1, VR18.2 (S)
unnamed: R35.1, VR19.2 (S)
unnamed: R36.1, VR20.2 (S)
unnamed: R14.1, R16.1, R33.2, U2.14 (OUT)

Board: 2 copper layers, 81 parts (15 on the bottom side), 49 nets, no tracks yet.
